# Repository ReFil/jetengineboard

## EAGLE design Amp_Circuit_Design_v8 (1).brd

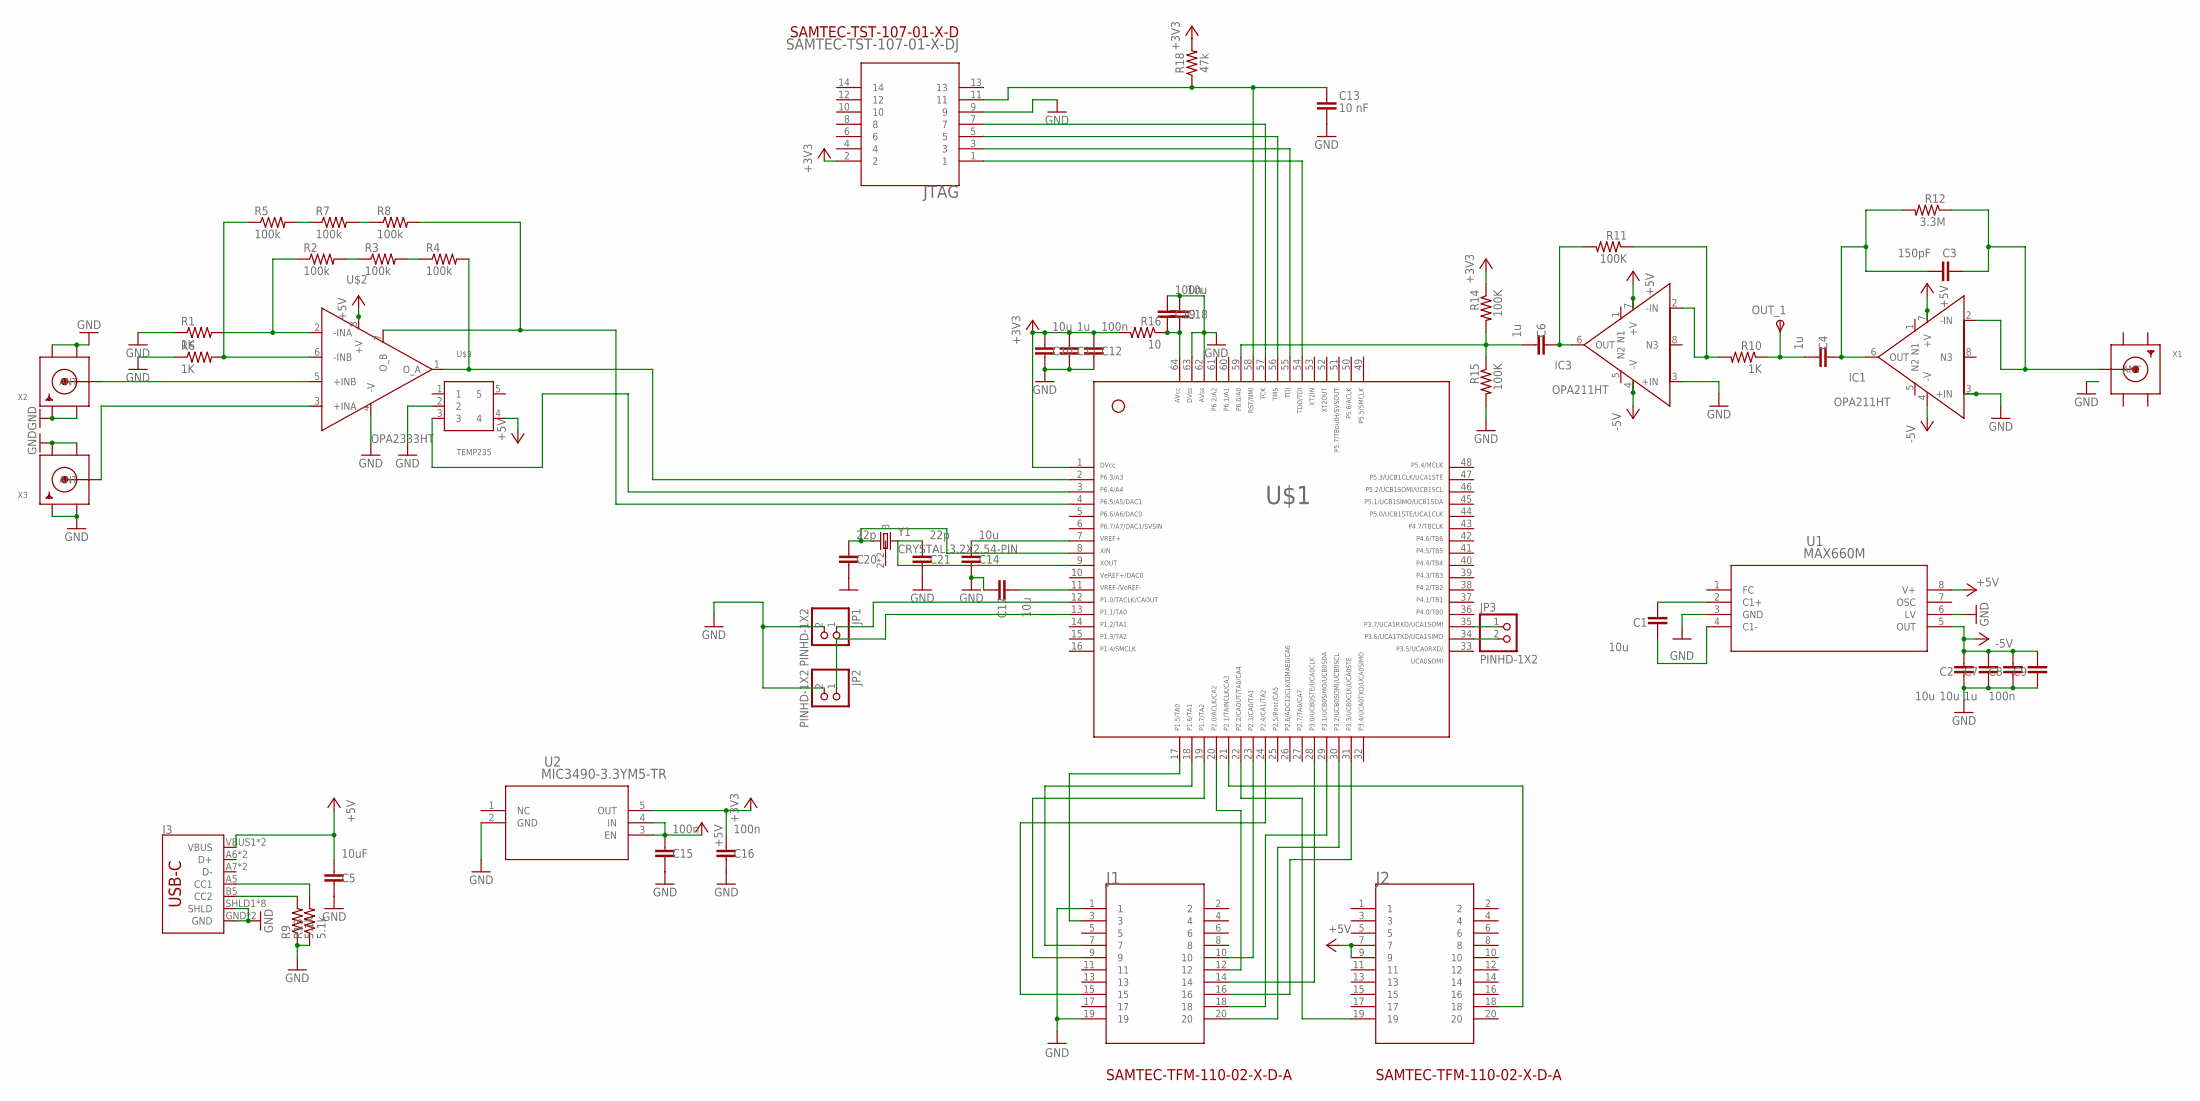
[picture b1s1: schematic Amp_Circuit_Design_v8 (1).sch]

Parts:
C1, C2, C7, C10, C14, C17, C18: 10u; 0603-C
C3: 150pF; 0603-C
C4, C6, C8, C11: 1u; 0603-C
C5: 10uF; 0603-C
C9, C12, C15, C16, C19: 100n; 0603-C
C13: 10 nF; 0603-C
C20, C21: 22p; 0603-C
IC1, IC3: OPA211HT; HKJ(R-CDFP-F8)
J1, J2: SAMTEC-TFM-110-02-X-D-AJ; SAMTEC-TFM-110-02-X-D-A
J3: SPARKFUN-CONNECTORS_USB_C16PIN; SPARKFUN-CONNECTORS_USB-C-16P
JP1, JP2, JP3: PINHD-1X2; 1X02
JTAG: SAMTEC-TST-107-01-X-DJ; SAMTEC-TST-107-01-X-D
OUT_1: TPSB1,27; B1,27
R1, R6, R10: 1K; 0603-R
R2, R3, R4, R5, R7, R8: 100k; 0603-R
R9, R13: 5.1k; 0603-R
R11, R14, R15: 100K; 0603-R
R12: 3.3M; 0603-R
R16: 10; 0603-R
R18: 47k; 0603-R
U1: MAX660M; M08A
U2: MIC3490-3.3YM5-TR; SOT-23-5_OT_MCH
U$1: F261X---PM64; PM/PAG64
U$2: OPA2333HT; D(R-PDSO-G8)
U$3: TEMP235; DCK(R-PDSO-G5)
X1, X2, X3: SMACONNECTOR_EDGE; SMA_EDGELAUNCH
Y1: CRYSTAL-3.2X2.54-PIN; XTAL-3.2X2.5

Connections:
+3V3: C10.2, C11.2, C12.2, C16.2, JTAG.2, R14.1, R16.2, R18.2, U2.5 (OUT), U$1.1
+5V: C5.2, C15.2, IC1.7 (+V), IC3.7 (+V), J2.7, J2.9, J3.VBUS1 (VBUS), J3.VBUS2 (VBUS), U1.8 (V+), U2.3 (EN), U2.4 (IN), U$2.8 (+V), U$3.4
-5V: C2.1, C7.1, C8.1, C9.1, IC1.4 (-V), IC3.4 (-V), U1.5 (OUT)
GND: C2.2, C5.1, C7.2, C8.2, C9.2, C10.1, C11.1, C12.1, C13.2, C14.1, C15.1, C16.1, C17.1, C18.2, C19.2, C20.1, C21.1, IC1.3 (+IN), IC3.3 (+IN), J1.1, J1.19, J3.GND, J3.GND2 (GND), J3.SHLD1 (SHLD), J3.SHLD2 (SHLD), J3.SHLD3 (SHLD), J3.SHLD4 (SHLD), J3.SHLD5 (SHLD), J3.SHLD6 (SHLD), J3.SHLD7 (SHLD), J3.SHLD8 (SHLD), JP1.2, JP2.2, JTAG.9, R1.1, R6.1, R9.1, R13.1, R15.2, U1.3 (GND), U1.6 (LV), U2.2 (GND), U$1.62, U$1.63, U$2.4 (-V), U$3.2, X2.GND@1 (GND4), X2.GND@2 (GND3), X2.GND@3 (GND2), X2.GND@4 (GND1), X3.GND@1 (GND4), X3.GND@2 (GND3), X3.GND@3 (GND2), X3.GND@4 (GND1)
GND1: X1.GND@4 (GND1)
GND2: X1.GND@3 (GND2)
GND3: X1.GND@2 (GND3)
GND4: X1.GND@1 (GND4)
unnamed: R8.2, U$1.4, U$2.7 (O_B)
unnamed: R4.2, U$1.2, U$2.1 (O_A)
unnamed: U$2.3 (+INA), X3.P (ANT)
unnamed: U$1.3, U$3.3
unnamed: R1.2, R2.1, U$2.2 (-INA)
unnamed: R5.1, R6.2, U$2.6 (-INB)
unnamed: U$2.5 (+INB), X2.P (ANT)
unnamed: C1.1, U1.2 (C1+)
unnamed: C3.2, C4.1, IC1.6 (OUT), R12.2
unnamed: C4.2, OUT_1.TP, R10.1
unnamed: R5.2, R7.1
unnamed: R2.2, R3.1
unnamed: R3.2, R4.1
unnamed: IC3.2 (-IN), R10.2, R11.1
unnamed: R7.2, R8.1
unnamed: J3.B5 (CC2), R9.2
unnamed: C6.2, R14.2, R15.1, U$1.59
unnamed: C3.1, IC1.2 (-IN), R12.1, X1.P (ANT)
unnamed: J1.14, U$1.28
unnamed: J3.A5 (CC1), R13.2
unnamed: JP1.1, U$1.12
unnamed: C14.2, U$1.7
unnamed: J1.18, U$1.29
unnamed: J1.20, U$1.30
unnamed: C6.1, IC3.6 (OUT), R11.2
unnamed: J1.16, U$1.31
unnamed: JTAG.1, U$1.54
unnamed: JTAG.3, U$1.55
unnamed: JTAG.5, U$1.56
unnamed: JTAG.7, U$1.57
unnamed: C1.2, U1.4 (C1-)
unnamed: JP3.1, U$1.35
unnamed: C13.1, JTAG.11, R18.1, U$1.58
unnamed: JP3.2, U$1.34
unnamed: C20.2, U$1.8, Y1.1
unnamed: C18.1, C19.1, R16.1, U$1.64
unnamed: C17.2, U$1.11
unnamed: JP2.1, U$1.13
unnamed: J1.3, U$1.17
unnamed: J1.7, U$1.18
unnamed: J1.9, U$1.19
unnamed: J1.12, U$1.20
unnamed: J2.18, U$1.21
unnamed: J2.19, U$1.22
unnamed: J1.10, U$1.23
unnamed: C21.2, U$1.9, Y1.3 (2)
unnamed: J1.15, U$1.24

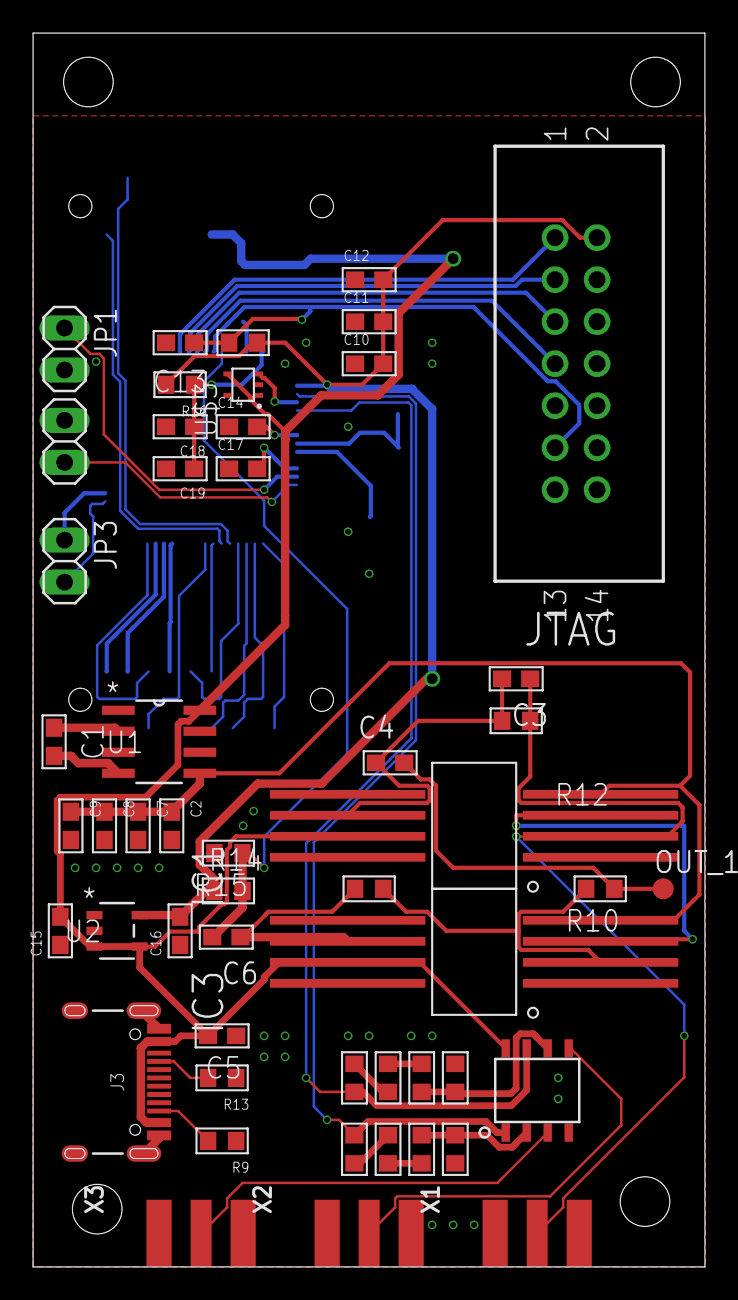
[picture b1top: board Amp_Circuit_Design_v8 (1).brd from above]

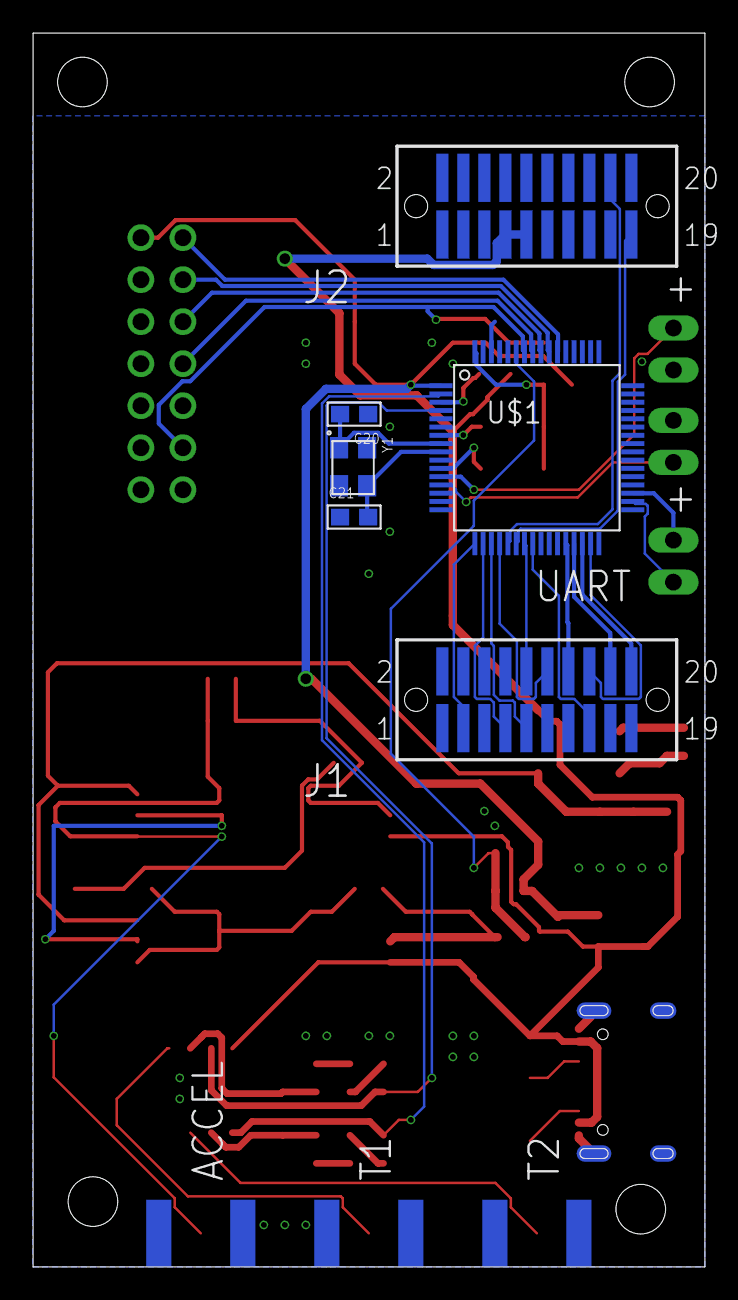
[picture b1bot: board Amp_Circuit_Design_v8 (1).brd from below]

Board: 2 copper layers, 40.6 x 74.6 mm, 57 parts (6 on the bottom side), 51 nets.

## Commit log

2021-08-21 added regulator
2021-08-21 added converter
2021-08-21 push
2021-08-21 added biasing
2021-08-22 PCB push

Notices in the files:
parts and their libraries:
COPYRIGHT: Copyright (C) 2018 Accelerated Designs. All rights reserved
